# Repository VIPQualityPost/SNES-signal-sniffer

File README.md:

# SNES-signal-sniffer
SNES logic analyzer breakout board. Used for debugging SNES carts in-situ with a logic analyzer. I have an HP1670D so the LA configuration file is written for that, but all pins are exposed and you can connect just the lines you need. There might be a bug with the CIC lines because some carts I use seem to reboot the SNES sporadically. I have not looked into the issue yet since mostly I was looking at bootcode, it did not effect my use. This was designed for use with the HP 1650-63203 termination adapter, although you could connect flying probe leads to the headers if you did not have these.

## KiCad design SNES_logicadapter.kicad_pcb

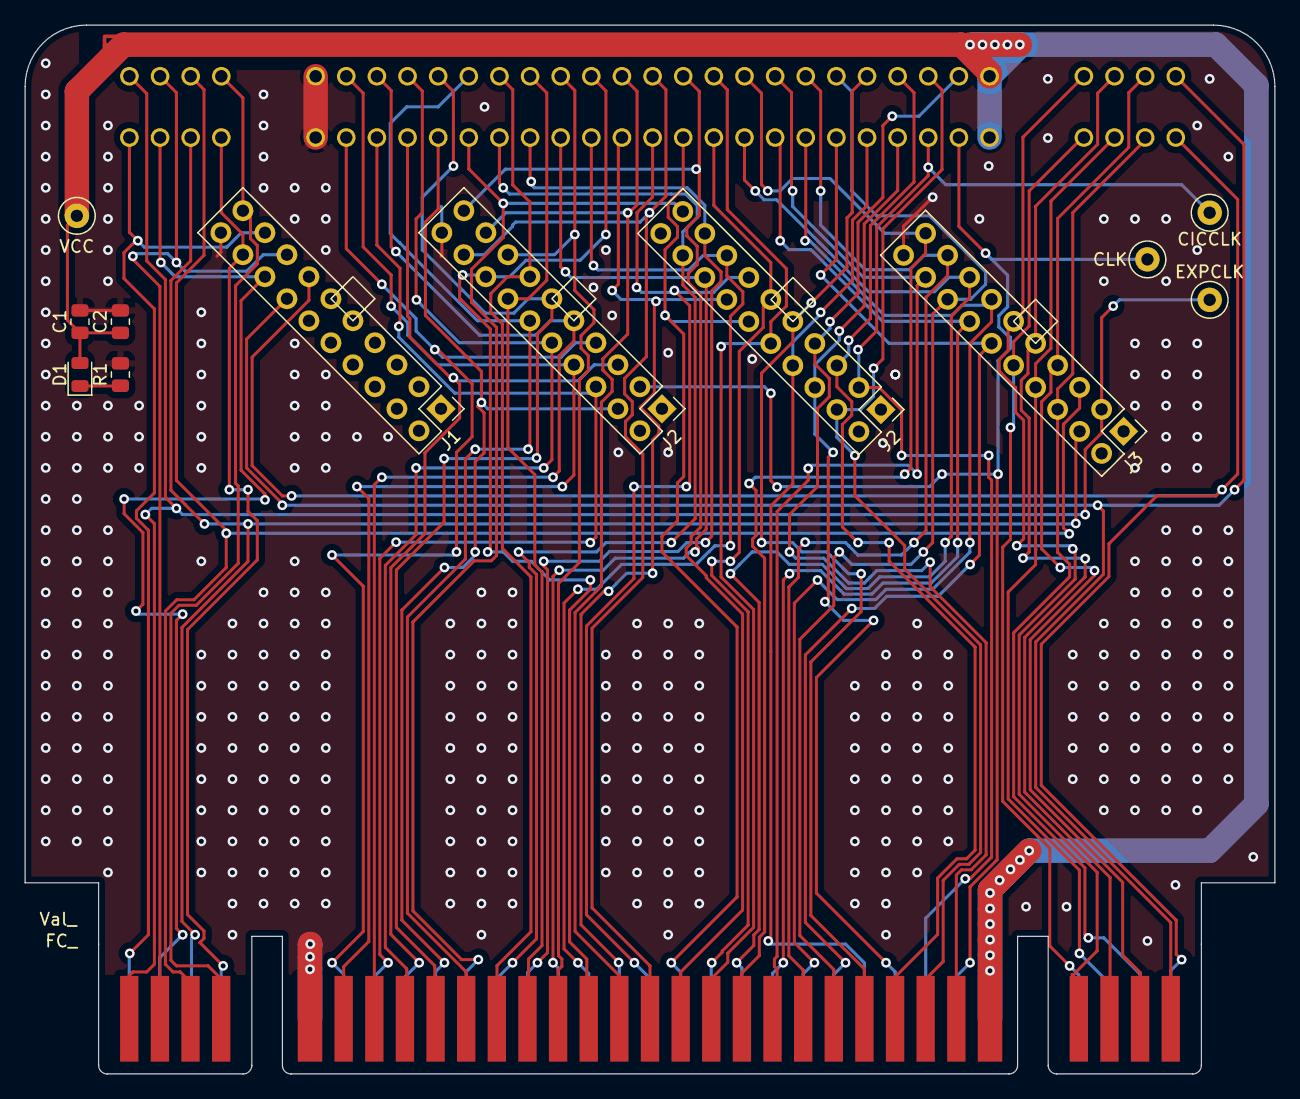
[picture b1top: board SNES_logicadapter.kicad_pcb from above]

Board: 2 copper layers, 102.0 x 85.6 mm, 15 parts (1 on the bottom side), 61 nets.

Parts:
C1: .1uF; R_0805_2012Metric
C2: 1uF; R_0805_2012Metric
CICCLK: CIC_CLK; TestPoint_Loop_D1.80mm_Drill1.0mm_Beaded
CLK: CLK; TestPoint_Loop_D1.80mm_Drill1.0mm_Beaded
CON1: SNES-CONN; SNESCART_EXT
CON2: SNES-CONN; SNES-CONN-EXP
D1: LED; D_0805_2012Metric
EXPCLK: EXPCLK; TestPoint_Loop_D1.80mm_Drill1.0mm_Beaded
FC_: Val_; SNES_logicadapter
J1, J2, J2#2, J3: HP_1650-63203_logicanalyzer; LAHeader_HP01650-63203
R1: 330; R_0805_2012Metric
VCC: Vcc; TestPoint_Loop_D1.80mm_Drill1.0mm_Beaded

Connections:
/A0: CON1.17 (A0), CON2.17 (A0), J2#2.19 (D0)
/A1: CON1.16 (A1), CON2.16 (A1), J2#2.18 (D1)
/A2: CON1.15 (A2), CON2.15 (A2), J2#2.17 (D2)
/A3: CON1.14 (A3), CON2.14 (A3), J2#2.16 (D3)
/A4: CON1.13 (A4), CON2.13 (A4), J2#2.15 (D4)
/A5: CON1.12 (A5), CON2.12 (A5), J2#2.14 (D5)
/A6: CON1.11 (A6), CON2.11 (A6), J2#2.13 (D6)
/A7: CON1.10 (A7), CON2.10 (A7), J2#2.12 (D7)
/A8: CON1.9 (A8), CON2.9 (A8), J2#2.11 (D8)
/A9: CON1.8 (A9), CON2.8 (A9), J2#2.10 (D9)
/A10: CON1.7 (A10), CON2.7 (A10), J2#2.9 (D10)
/A11: CON1.6 (A11), CON2.6 (A11), J2#2.8 (D11)
/A12: CON1.37 (A12), CON2.37 (A12), J2#2.7 (D12)
/A13: CON1.38 (A13), CON2.38 (A13), J2#2.6 (D13)
/A14: CON1.39 (A14), CON2.39 (A14), J2#2.5 (D14)
/A15: CON1.40 (A15), CON2.40 (A15), J2#2.4 (D15)
/AUDIO_L: CON1.31 (AUDIO_L), CON2.31 (AUDIO_L), J1.14 (D5)
/AUDIO_R: CON1.62 (AUDIO_R), CON2.62 (AUDIO_R), J1.13 (D6)
/BA0: CON1.41 (BA0), CON2.41 (BA0), J2.19 (D0)
/BA1: CON1.42 (BA1), CON2.42 (BA1), J2.18 (D1)
/BA2: CON1.43 (BA2), CON2.43 (BA2), J2.17 (D2)
/BA3: CON1.44 (BA3), CON2.44 (BA3), J2.16 (D3)
/BA4: CON1.45 (BA4), CON2.45 (BA4), J2.15 (D4)
/BA5: CON1.46 (BA5), CON2.46 (BA5), J2.14 (D5)
/BA6: CON1.47 (BA6), CON2.47 (BA6), J2.13 (D6)
/BA7: CON1.48 (BA7), CON2.48 (BA7), J2.12 (D7)
/CIC_CLK: CICCLK.1, CON1.56 (CIC_CLK), CON2.56 (CIC_CLK), J2.3 (CLK1)
/CIC_IN: CON1.55 (CIC_IN), CON2.55 (CIC_IN), J2.6 (D13)
/CIC_OUT: CON1.24 (CIC_OUT), CON2.24 (CIC_OUT), J2.5 (D14)
/CIC/RST: CON1.25 (CIC_RST), CON2.25 (CIC_RST), J2.4 (D15)
/CLK: CLK.1, CON1.57 (CPU_CLK), CON2.57 (CPU_CLK), J2#2.3 (CLK1)
/D0: CON1.19 (D0), CON2.19 (D0), J3.19 (D0)
/D1: CON1.20 (D1), CON2.20 (D1), J3.18 (D1)
/D2: CON1.21 (D2), CON2.21 (D2), J3.17 (D2)
/D3: CON1.22 (D3), CON2.22 (D3), J3.16 (D3)
/D4: CON1.50 (D4), CON2.50 (D4), J3.15 (D4)
/D5: CON1.51 (D5), CON2.51 (D5), J3.14 (D5)
/D6: CON1.52 (D6), CON2.52 (D6), J3.13 (D6)
/D7: CON1.53 (D7), CON2.53 (D7), J3.12 (D7)
/EXPAND: CON1.2 (EXPAND), CON2.2 (EXPAND), J1.15 (D4)
/EXPCLK: CON1.1 (CLK_21.477MHz), CON2.1 (CLK_21.477MHz), EXPCLK.1, J3.3 (CLK1)
/PA0: CON1.28 (PA0), CON2.28 (PA0), J3.11 (D8)
/PA1: CON1.59 (PA1), CON2.59 (PA1), J3.10 (D9)
/PA2: CON1.29 (PA2), CON2.29 (PA2), J3.9 (D10)
/PA3: CON1.60 (PA3), CON2.60 (PA3), J3.8 (D11)
/PA4: CON1.30 (PA4), CON2.30 (PA4), J3.7 (D12)
/PA5: CON1.61 (PA5), CON2.61 (PA5), J3.6 (D13)
/PA6: CON1.3 (PA6), CON2.3 (PA6), J3.5 (D14)
/PA7: CON1.34 (PA7), CON2.34 (PA7), J3.4 (D15)
/REFRESH: CON1.33 (REFRESH), CON2.33 (REFRESH), J1.16 (D3)
//CE: CON1.49 (~CE), CON2.49 (~CE), J2.11 (D8)
//IRQ: CON1.18 (~IRQ), CON2.18 (~IRQ), J2.10 (D9)
//PARD: CON1.4 (~PARD), CON2.4 (~PARD), J1.19 (D0)
//PAWR: CON1.35 (~PAWR), CON2.35 (~PAWR), J1.18 (D1)
//RD: CON1.23 (~RD), CON2.23 (~RD), J2.9 (D10)
//RESET: CON1.26 (~RESET), CON2.26 (~RESET), J2.7 (D12)
//WR: CON1.54 (~WR), CON2.54 (~WR), J2.8 (D11)
//WRAM: CON1.32 (~WRAM), CON2.32 (~WRAM), J1.17 (D2)
GND: C1.2, C2.2, CON1.5 (GND), CON1.36 (GND), CON2.5 (GND), CON2.36 (GND), J1.20 (GND), J2.20 (GND), J2#2.20 (GND), J3.20 (GND), R1.2
unnamed: D1.1 (K), R1.1
VCC: C1.1, C2.1, CON1.27 (Vcc), CON1.58 (Vcc), CON2.27 (Vcc), CON2.58 (Vcc), D1.2 (A), VCC.1

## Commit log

2022-11-18 added files
2022-11-18 add logic analyzer config
2023-02-13 Auto-commit Mon Feb 13 12:20:08 EST 2023
2023-02-17 Auto-commit Thu Feb 16 21:34:58 EST 2023
2023-02-17 Auto-commit Fri Feb 17 12:27:47 EST 2023
2023-02-17 Auto-commit Fri Feb 17 13:04:04 EST 2023
2023-02-17 Remove ignored files
2023-02-18 Auto-commit Fri Feb 17 21:15:47 EST 2023
2023-04-11 Auto-commit Tue Apr 11 10:47:21 EDT 2023
2023-04-30 Auto-commit Sun Apr 30 10:54:44 EDT 2023
2023-05-14 Auto-commit Sun May 14 18:30:08 EDT 2023
